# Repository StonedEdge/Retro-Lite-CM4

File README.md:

# Retro Lite CM4: Raspberry Pi Handheld

## Description
 
The Retro Lite CM4 is a joint project between Dmcke5 and StonedEdge. The console is powered by a 4000mAh Li-Po and is designed to run with various software images, including but not limited to RetroPie, Lakka or Batocera, directly from an SD card or via eMMC storage. The project housing was inspired by a Nintendo Switch Lite, but is not a 100% match to the original. The CM4 cannot currently emulate most 32/64-bit consoles released after the PSP or Dreamcast. This means GameCube, Wii and 3DS are currently unplayable until the Foundation releases a newer version of the Compute Module line. wiringPi is now a deprecated GPIO library however does work with arm64 and aarch64, so you can install 64-bit RetroPie if you'd like. 

## Features

- Machined aluminum 6061 housing (green/purple), custom machined and anodized by Dmcke5
- Raspberry Pi 4 SoC: Broadcom BCM2711 quad-core Cortex-A72 @ 1.5GHz (ARM CPU overclockable to 2.1GHz, GPU overclockable to 850MHz)
- 2GB of LPDDR4-3200 SDRAM
- 5.0GHz IEEE 802.11b/g/n/ac wireless, Bluetooth 5.0
- Custom AIO 4-layer PCB, with CM4 mezzanines, 5v boost rated at 2.1A continuous current, 3.3v buck, USB2422 hub, BQ24292i, MAX17055 fuel gauge, ATtiny84, WM8960 amp, TFP401 encoder, SD card slot, USB-C hardware and mini HDMI type A
- 2x controller PCBs with FFC cables
- 800 x 480 (5:3 aspect ratio) IPS display
- HDMI video output (HDMI0 - internal)
- 1080p 60fps HDMI video output (HDMI1 - external) via the mini HDMI port
- Tempered glass screen protector
- Fuel gauge for accurate battery SoC monitoring - MAX17055, custom battery indicator shown in steps of 10 icons, plus %SoC value, via dispmanx APIs on a TFT HDMI driven panel
- Charging indicator
- HDMI switching scripts, to shutdown and reboot to external HDMI with an overclock applied
- ATMEGA32u4 internal USB 2.0 HID controller
- Brightness and volume HUD adjustment, in steps of 10 icons. Brightness is adjusted by holding select + up/down on the DPAD
- Custom menu, activated by pushing select + R3. The menu consists of 4 sections (1. Battery Information, 2. Controller Calibration, 3. Onscreen Keyboard, 4. Settings Menu) -   courtesy of Dmcke5's hard work and ideas :D
- USB-C PD charging capabilities up to 15v (0.5C charge rate at 2A) with an original Nintendo Switch charger
- Stereo Audio Output via i2s WM8960 Wolfson audio amplifier
- Headphone jack, with automatic switching
- 4000mAh custom lipo design, providing 4 hours of gameplay
- Dual stacked shoulder buttons (L, R, LZ, RZ)
- 2x switch analog sticks, range programmable in software
- Resin casted ABXY, DPAD, start+select, shoulder buttons with acetal spring hinge + silicone membranes
- Safe software/hardware shutdown to prevent corruption to the SD card data (low voltage shutdown included)
- USB 2.0 2-port downstream hub
- External dock passthrough PCB with 4 port USB-hub - have now started uploading dock assets

Click the link below to view a more detailed buildlog of the Retro Lite CM4: 
https://bitbuilt.net/forums/index.php?threads/retro-lite-cm4-a-stonededge-and-dmcke5-collaboration.3934/

## Requirements to Build the Retro Lite CM4

### Code 

Code has now been split into various header files and the retrolite.c code has now been made easier to read and condensed for the end-user. Code required to complete the handheld includes an ATtiny84 monitor script, which can be flashed via the 1.27mm pitch 6 pin header on the main Retro Lite PCB with an Arduino or similar programmer. Code for the i2s audio amplifier, fuel gauge and OSD functionality can be compiled directly on the CM4 module from the command line. Current code is unfinished as of January 2022, however we are pushing bug fixes when we find them - expect a fully functioning RetroPie image to be shared in the future from this repository (actually, just found out this is not allowed due to the licensing of certain emulators, so will create install scripts at a later date). 

To flash the software to the Retro Lite CM4, you can either download the latest RetroPie Retro Lite custom image, or follow the below steps to get up and running. Plan is to eventually put this into a single script. I have not currently tested our firmware on images other than RetroPie, however I assume other images should also work fine. 

a) Download the latest version of RetroPie for the Raspberry Pi 4/400 here (also compatible with CM4): 
https://retropie.org.uk/download/ 

b) Run the WM8960 I2S audio amplifier script and install audio drivers:
https://github.com/StonedEdge/seeed-voicecard

c) Install the latest version of WiringPi, compatible with both 64/32-bit OS here: 
https://github.com/StonedEdge/WiringPi

d) Add config.txt to the /boot directory (overwrite)

e) cd /home/pi/RetroliteOSD sudo make - compile the Retro Lite CM4 C code and generate binary

f) Navigate to the /etc directory and add the below lines to the rc.local file, to allow the code to run every time at startup 

cd /home/pi/RetroliteOSD
sudo ./retrolite &
sudo ./hdmi_script.sh & 

g) sudo reboot - Reboot to enable all changes 

You should now have all the required software installed for the Retro Lite CM4 to display battery SoC, charging status, WiFi status, bluetooth status and more. The Retro Lite CM4 automatically safely shuts itself down when the voltage of the batteries depletes to 3.1V - adjustable directly from the settings calibration menu. The Retro Lite CM4 must reboot to output video to an external monitor via the mini HDMI type-A port, which is handled by the hdmi_switch.sh script. 

-------------------------------------------------------------------------------------------------------

### CAD
The CAD files for the Retro Lite CM4 are now available and open source! Please do give credit where due as a lot of work has gone into these designs.
You can check out my project partner's work here: https://github.com/dmcke5

-------------------------------------------------------------------------------------------------------

### PCB
The Retro Lite CM4 requires 4 custom designed PCBs to be installed, not including the CM4 carrier board. These include: 

a) Retro Lite CM4 AIO carrier board 

b) Retro Lite Controller PCB (Right)

c) Retro Lite Controller PCB (Left)

d) Retro Lite Button Daughterboard

Gerbers to be ordered from your board house of choice have now been uploaded! Recommended to use JLCPCB for fast turnaround using their 4-layer service.

-------------------------------------------------------------------------------------------------------

### BOM (Bill of Materials) 
Preliminary BOMs for all 4 PCBs have been added including cost. You will have to source your own parts however most can be found on Digikey/Mouser.

-------------------------------------------------------------------------------------------------------
### New Revision Features
Features that I would like to add to the handheld (welcome for others to assist) include the following:

a) HDMI over USB-C, using the TPS65987D and the TUSB546A-DCI high speed mux. 

b) OTG integration (power perihperals through the onboard USB-C port). 

c) DSI 5.5" display (struggle to know of a way to get this working currently on the Pi). 

Feel free to make a pull request with any changes you would like seen to the handheld. 

-------------------------------------------------------------------------------------------------------

### FAQs
Q: How can I get my hands one of these handhelds? Do you sell them? 

A: I am not currently selling kits on this handheld (nor do I plan to for the forseeable future), but I do offer commissions on occassion via my social media. DM me for details. 

Q: Why dont you use a 5.5" display from a Switch Lite? 

A: MIPI reverse engineering is not simple not trivial to a hobbyist like myself. 

Q: Why are your commissions ludicrously priced?

A: Building one off handhelds for people is expensive. Labor & parts dont come cheap either. I'd recommend you build one yourself using the assets from this GitHub or just buy a mass produced emulation handheld from Aliexpress. 

### Optional Docking Station 

Source code available here:
https://github.com/StonedEdge/Retro-Lite-CM4-Dock

The docking station is now completed! It's designed to work with RetroPie and use a RP2040 microcontroller, written in C (Pico) and Python (CM4). Feel free to build one if you'd like! 

-------------------------------------------------------------------------------------------------------
### Contributors 
I'd like to thank these people in no particular order for the awesome work you have done to help me complete this project. 

* Dmcke5 for designing the case assets, including machining/anodizing the prototypes, doing most of the code and much more. Wouldn't have been possible to complete this without you - a team effort
* YveltalGriffin/Mackie-Kannard Smith, for suggesting various hardware changes and reviews to PCB/schematics + GitHub bugs. His help was invaluable in learning new things about PCB design 
* Juckett D, for creating the Aegis CM4 and offering tips and tricks along the way. Check out his work here and awesome CM4 handheld(s): https://github.com/juckettd
* Aurelio Manarra, for always helping me out with my non EE questions and various other things ᕕ( ᐛ )ᕗ
* Bill, for helping me with the docking station code & bug fixes

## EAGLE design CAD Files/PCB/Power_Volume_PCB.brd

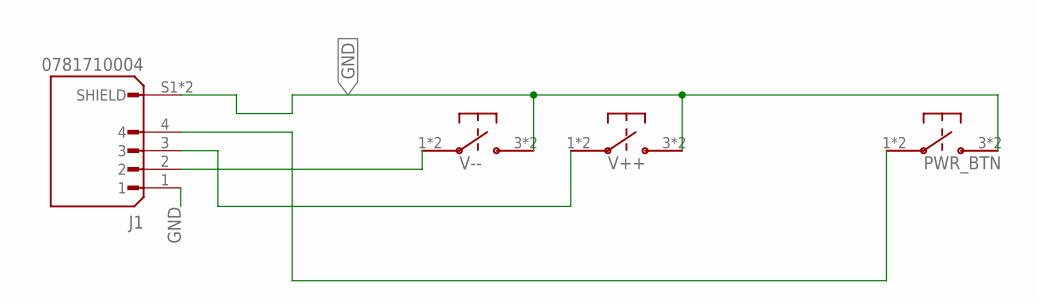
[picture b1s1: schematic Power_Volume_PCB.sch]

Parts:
J1: 0781710004; MOLEX_0781710004
PWR_BTN: TL3315NF100Q
V++: TL3315NF100Q
V--: TL3315NF100Q

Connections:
GND: J1.1, J1.S1 (SHIELD), J1.S2 (SHIELD), PWR_BTN.3, PWR_BTN.4, V++.3, V++.4, V--.3, V--.4
unnamed: J1.4, PWR_BTN.1, PWR_BTN.2
unnamed: J1.3, V++.1, V++.2
unnamed: J1.2, V--.1, V--.2

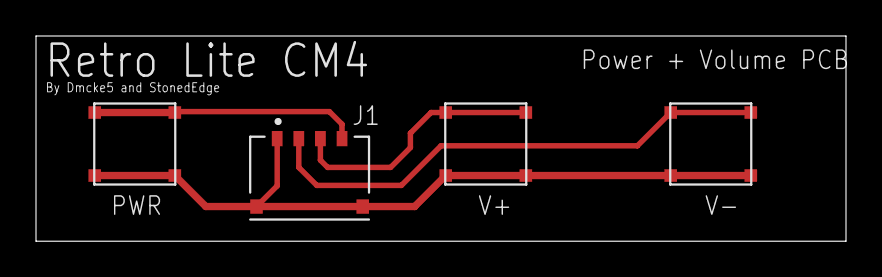
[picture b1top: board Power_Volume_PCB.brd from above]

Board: 2 copper layers, 45.0 x 11.4 mm, 4 parts (0 on the bottom side), 4 nets.

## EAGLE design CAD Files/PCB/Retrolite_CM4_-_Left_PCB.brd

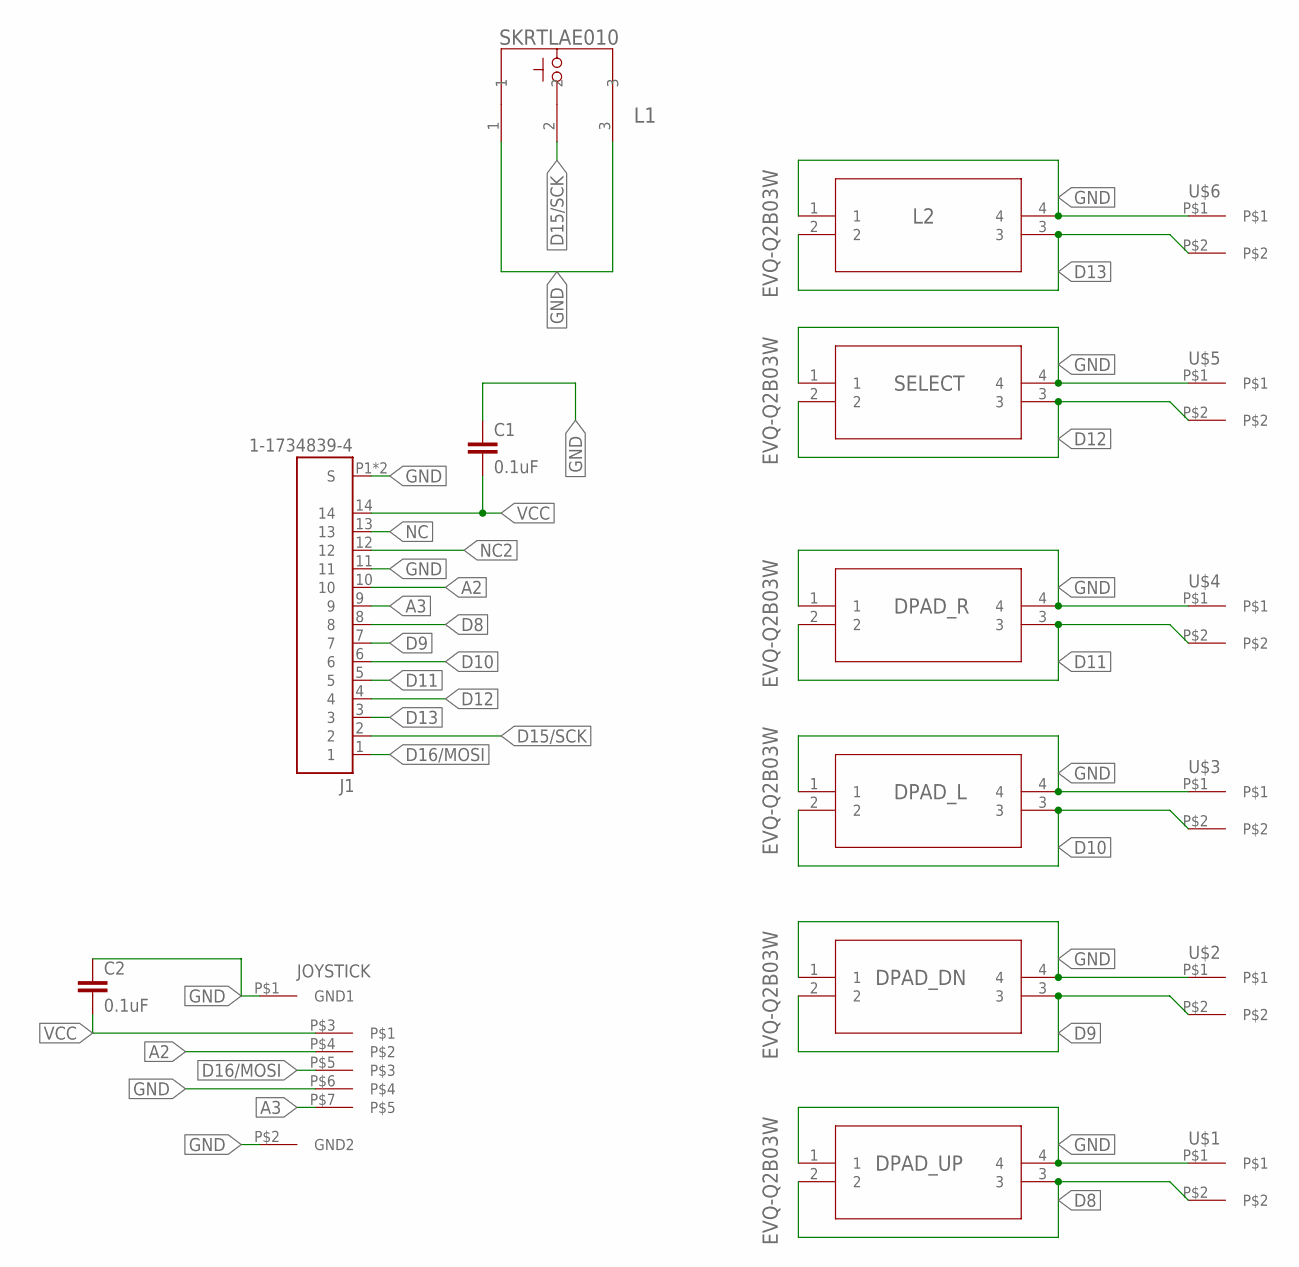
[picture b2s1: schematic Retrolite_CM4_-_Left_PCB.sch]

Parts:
C1, C2: 0.1uF; 0603
DPAD_DN: EVQ-Q2B03W; EVQQ2_3
DPAD_L: EVQ-Q2B03W; EVQQ2_3
DPAD_R: EVQ-Q2B03W; EVQQ2_3
DPAD_UP: EVQ-Q2B03W; EVQQ2_3
J1: 1-1734839-4; TE_1-1734839-4
JOYSTICK: 0545500571
L1: SKRTLAE010; SW3_SKRTLAE010_ALPS
L2: EVQ-Q2B03W; EVQQ2_3
SELECT: EVQ-Q2B03W; EVQQ2_3
U$1, U$2, U$3, U$4, U$5, U$6: MEMBRANEBUTTON

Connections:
A2: J1.10, JOYSTICK.P$4
A3: J1.9, JOYSTICK.P$7
D8: DPAD_UP.2, DPAD_UP.3, J1.8, U$1.P$2
D9: DPAD_DN.2, DPAD_DN.3, J1.7, U$2.P$2
D10: DPAD_L.2, DPAD_L.3, J1.6, U$3.P$2
D11: DPAD_R.2, DPAD_R.3, J1.5, U$4.P$2
D12: J1.4, SELECT.2, SELECT.3, U$5.P$2
D13: J1.3, L2.2, L2.3, U$6.P$2
D15/SCK: J1.2, L1.2
D16/MOSI: J1.1, JOYSTICK.P$5
GND: C1.1, C2.1, DPAD_DN.1, DPAD_DN.4, DPAD_L.1, DPAD_L.4, DPAD_R.1, DPAD_R.4, DPAD_UP.1, DPAD_UP.4, J1.11, J1.P1 (S), J1.P2 (S), JOYSTICK.P$1 (GND1), JOYSTICK.P$2 (GND2), JOYSTICK.P$6, L1.1, L1.3, L2.1, L2.4, SELECT.1, SELECT.4, U$1.P$1, U$2.P$1, U$3.P$1, U$4.P$1, U$5.P$1, U$6.P$1
NC: J1.13
NC2: J1.12
VCC: C1.2, C2.2, J1.14, JOYSTICK.P$3

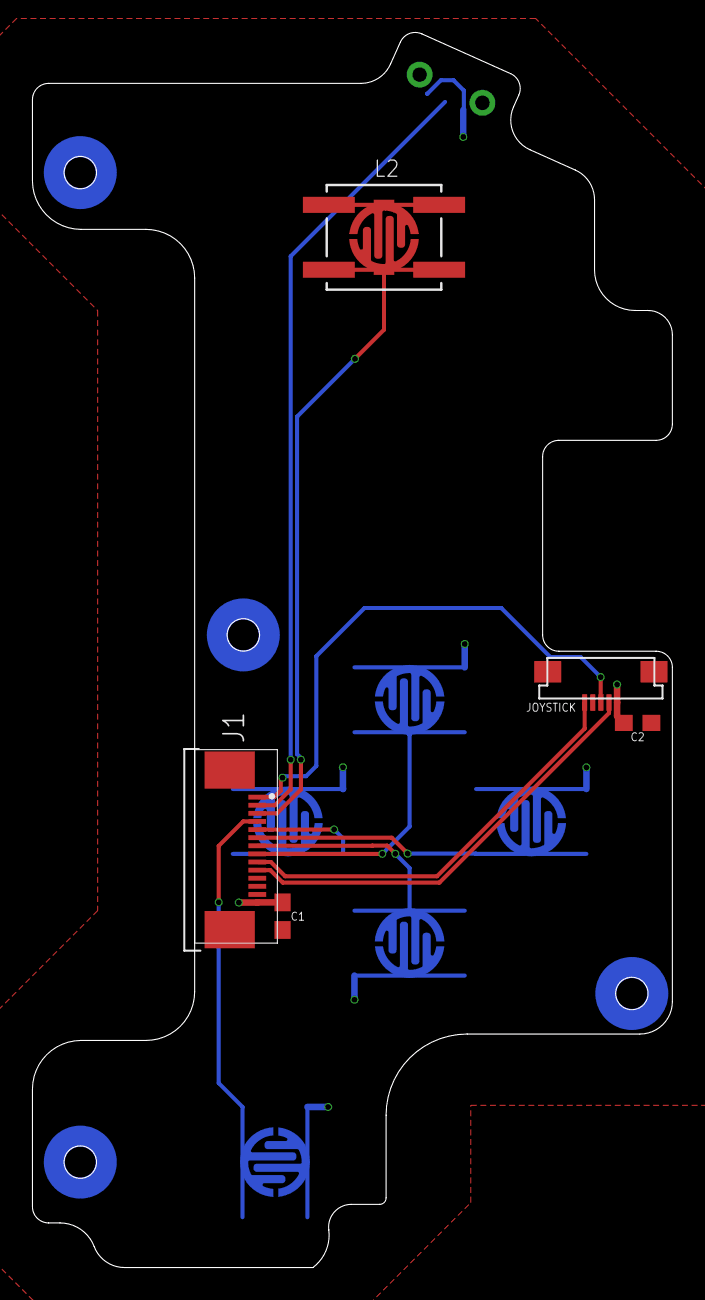
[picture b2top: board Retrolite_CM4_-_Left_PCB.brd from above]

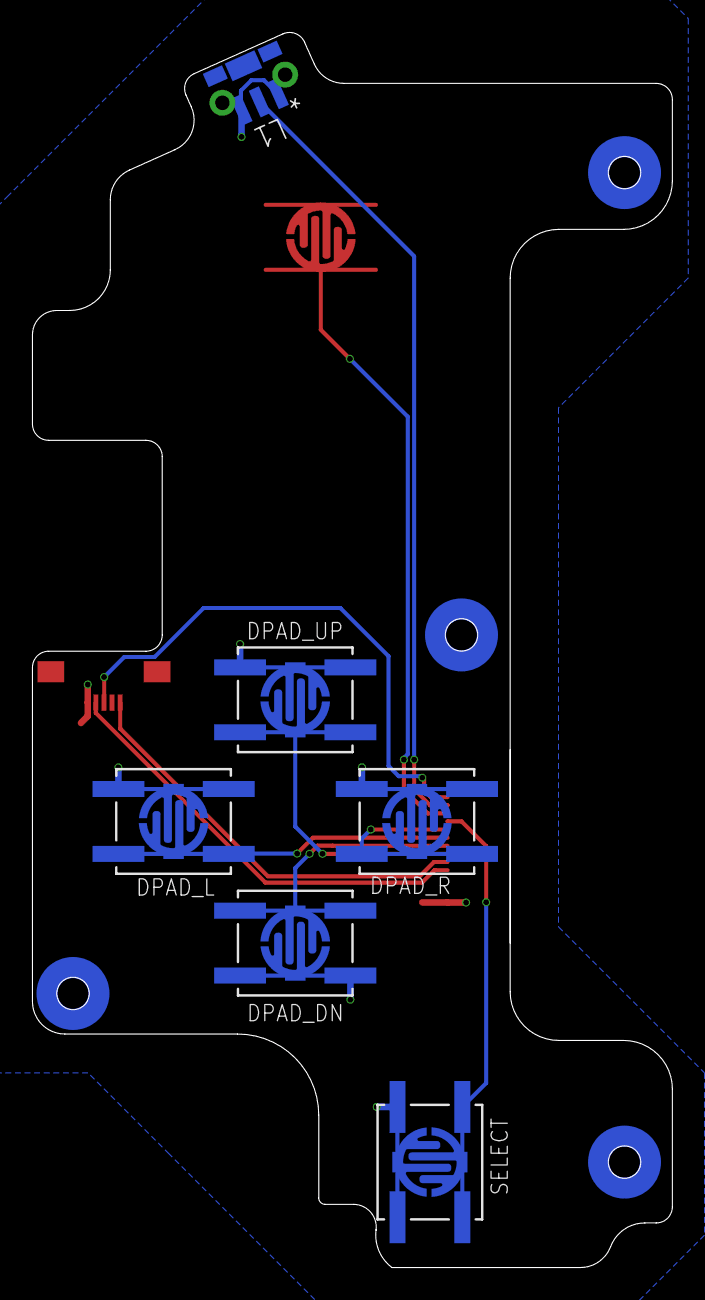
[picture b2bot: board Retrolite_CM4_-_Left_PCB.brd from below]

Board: 2 copper layers, 39.5 x 76.1 mm, 17 parts (11 on the bottom side), 12 nets.

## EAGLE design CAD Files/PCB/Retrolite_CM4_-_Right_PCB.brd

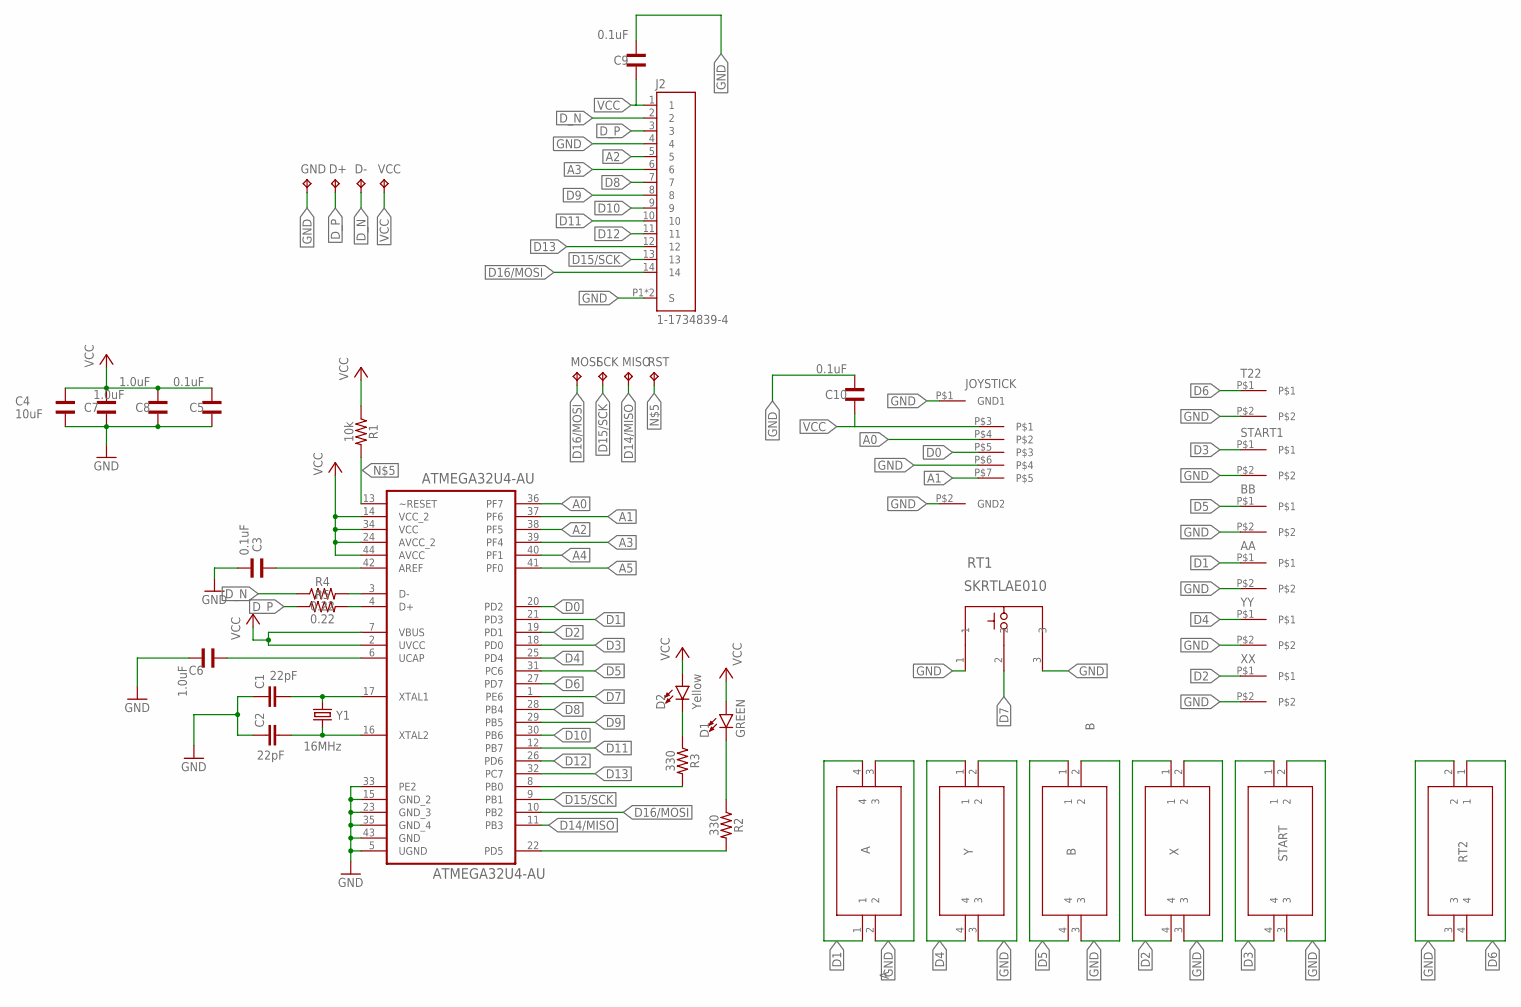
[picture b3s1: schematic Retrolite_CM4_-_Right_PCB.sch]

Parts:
A: A; EVQQ2_3
AA: MEMBRANEBUTTON
ATMEGA32U4-AU: ATMEGA32U4-AU; QFP80P1200X1200X120-44N
B: B; EVQQ2_3
BB: MEMBRANEBUTTON
C1, C2: 22pF; 0603
C3, C5, C9, C10: 0.1uF; WCAP-CSGP_0805_WAVE
C4: 10uF; WCAP-CSGP_0805_WAVE
C6, C7, C8: 1.0uF; WCAP-CSGP_0805_WAVE
D1: GREEN; LED-0603
D2: Yellow; LED-0603
D+: TPB1,27; B1,27
D-: TPB1,27; B1,27
GND: TPB1,27; B1,27
J2: 1-1734839-4; TE_1-1734839-4
JOYSTICK: 0545500571
MISO: TPB1,27; B1,27
MOSI: TPB1,27; B1,27
R1: 10k; 0603
R2, R3: 330; 0603
R4, R5: 0.22; 0805
RST: TPB1,27; B1,27
RT1: SKRTLAE010; SW3_SKRTLAE010_ALPS
RT2: T2; EVQQ2_3
SCK: TPB1,27; B1,27
START: START; EVQQ2_3
START1: MEMBRANEBUTTON
T22: MEMBRANEBUTTON
VCC: TPB1,27; B1,27
X: X; EVQQ2_3
XX: MEMBRANEBUTTON
Y: Y; EVQQ2_3
Y1: 16MHz; CRYSTAL-SMD-5X3.2-4PAD
YY: MEMBRANEBUTTON

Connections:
A0: ATMEGA32U4-AU.36 (PF7), JOYSTICK.P$4
A1: ATMEGA32U4-AU.37 (PF6), JOYSTICK.P$7
A2: ATMEGA32U4-AU.38 (PF5), J2.5
A3: ATMEGA32U4-AU.39 (PF4), J2.6
A4: ATMEGA32U4-AU.40 (PF1)
A5: ATMEGA32U4-AU.41 (PF0)
D0: ATMEGA32U4-AU.20 (PD2), JOYSTICK.P$5
D1: A.1, A.4, AA.P$1, ATMEGA32U4-AU.21 (PD3)
D2: ATMEGA32U4-AU.19 (PD1), X.1, X.4, XX.P$1
D3: ATMEGA32U4-AU.18 (PD0), START.1, START.4, START1.P$1
D4: ATMEGA32U4-AU.25 (PD4), Y.1, Y.4, YY.P$1
D5: ATMEGA32U4-AU.31 (PC6), B.1, B.4, BB.P$1
D6: ATMEGA32U4-AU.27 (PD7), RT2.1, RT2.4, T22.P$1
D7: ATMEGA32U4-AU.1 (PE6), RT1.2
D8: ATMEGA32U4-AU.28 (PB4), J2.7
D9: ATMEGA32U4-AU.29 (PB5), J2.8
D10: ATMEGA32U4-AU.30 (PB6), J2.9
D11: ATMEGA32U4-AU.12 (PB7), J2.10
D12: ATMEGA32U4-AU.26 (PD6), J2.11
D13: ATMEGA32U4-AU.32 (PC7), J2.12
D14/MISO: ATMEGA32U4-AU.11 (PB3), MISO.TP
D15/SCK: ATMEGA32U4-AU.9 (PB1), J2.13, SCK.TP
D16/MOSI: ATMEGA32U4-AU.10 (PB2), J2.14, MOSI.TP
D_N: D-.TP, J2.2, R4.1
D_P: D+.TP, J2.3, R5.1
GND: A.2, A.3, AA.P$2, ATMEGA32U4-AU.5 (UGND), ATMEGA32U4-AU.15 (GND_2), ATMEGA32U4-AU.23 (GND_3), ATMEGA32U4-AU.33 (PE2), ATMEGA32U4-AU.35 (GND_4), ATMEGA32U4-AU.43 (GND), B.2, B.3, BB.P$2, C1.1, C2.1, C3.1, C4.1, C5.2, C6.1, C7.2, C8.2, C9.1, C10.1, GND.TP, J2.4, J2.P1 (S), J2.P2 (S), JOYSTICK.P$1 (GND1), JOYSTICK.P$2 (GND2), JOYSTICK.P$6, RT1.1, RT1.3, RT2.2, RT2.3, START.2, START.3, START1.P$2, T22.P$2, X.2, X.3, XX.P$2, Y.2, Y.3, YY.P$2
unnamed: ATMEGA32U4-AU.17 (XTAL1), C1.2, Y1.1
unnamed: ATMEGA32U4-AU.42 (AREF), C3.2
unnamed: ATMEGA32U4-AU.6 (UCAP), C6.2
unnamed: ATMEGA32U4-AU.16 (XTAL2), C2.2, Y1.3 (2)
unnamed: ATMEGA32U4-AU.13 (~RESET), R1.2, RST.TP
unnamed: ATMEGA32U4-AU.22 (PD5), R2.2
unnamed: ATMEGA32U4-AU.8 (PB0), R3.2
unnamed: D1.C, R2.1
unnamed: D2.C, R3.1
USB_N: ATMEGA32U4-AU.3 (D-), R4.2
USB_P: ATMEGA32U4-AU.4 (D+), R5.2
VCC: ATMEGA32U4-AU.2 (UVCC), ATMEGA32U4-AU.7 (VBUS), ATMEGA32U4-AU.14 (VCC_2), ATMEGA32U4-AU.24 (AVCC_2), ATMEGA32U4-AU.34 (VCC), ATMEGA32U4-AU.44 (AVCC), C4.2, C5.1, C7.1, C8.1, C9.2, C10.2, D1.A, D2.A, J2.1, JOYSTICK.P$3, R1.1, VCC.TP

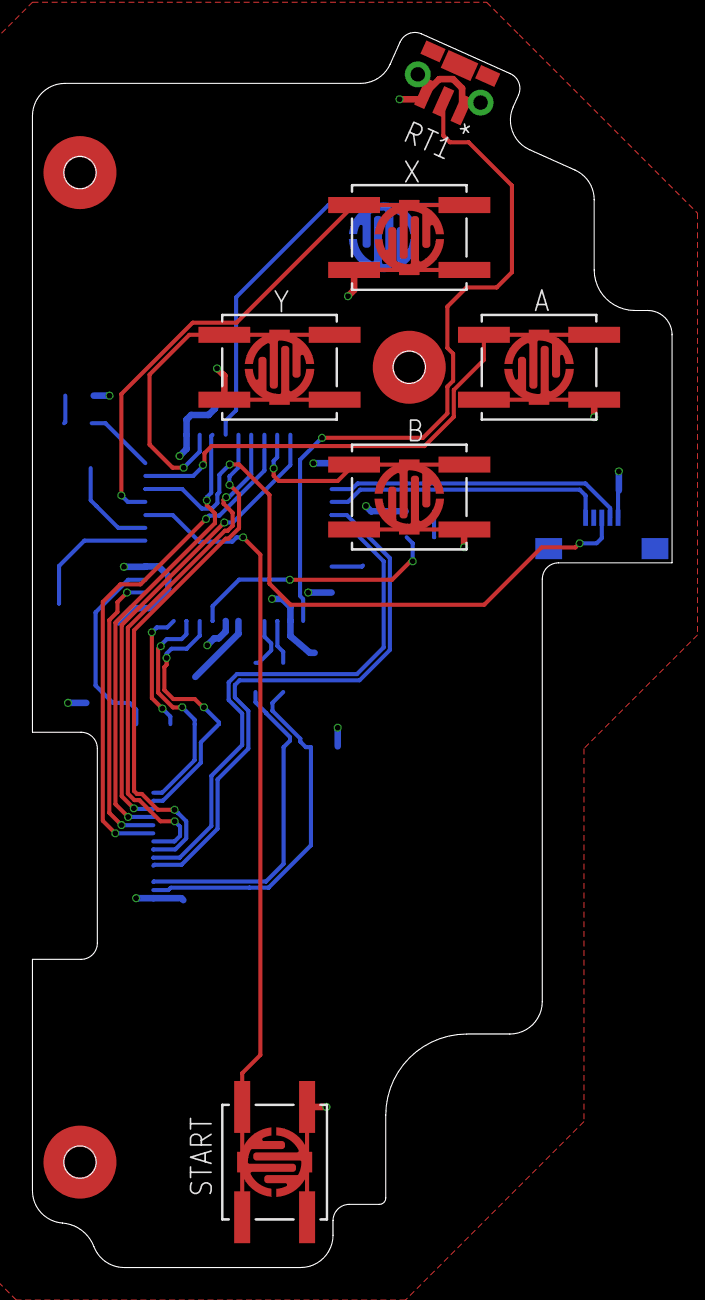
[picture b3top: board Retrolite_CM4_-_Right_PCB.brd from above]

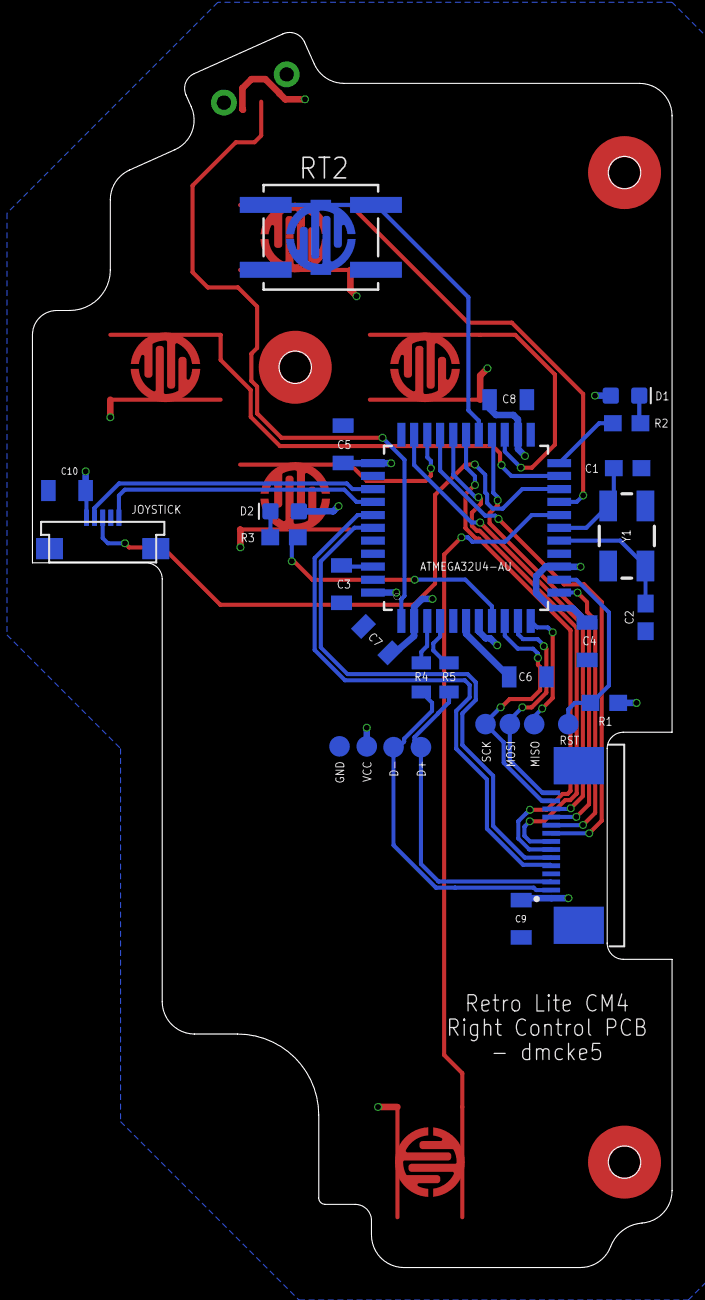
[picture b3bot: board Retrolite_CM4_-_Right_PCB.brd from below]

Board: 2 copper layers, 39.4 x 76.1 mm, 42 parts (31 on the bottom side), 36 nets.

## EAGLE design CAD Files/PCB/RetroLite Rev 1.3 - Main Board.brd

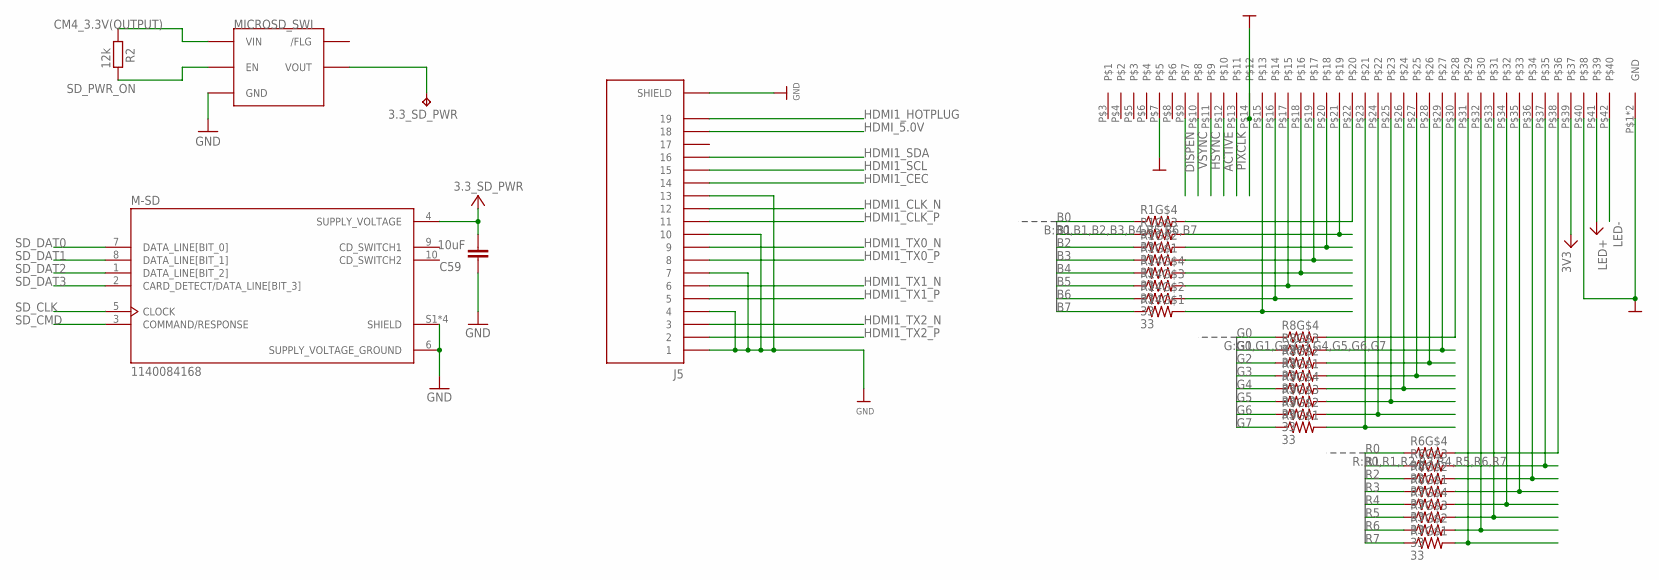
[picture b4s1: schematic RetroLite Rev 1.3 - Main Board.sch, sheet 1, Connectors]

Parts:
3.3_SD_PWR: TPTP07R; TP07R
C59: 10uF; 0805
J5: 685119136923; WURTH_685119136923
M-SD: 1140084168; AMPHENOL_1140084168
MICROSD_SWI: IC-RT9742
R1, R6, R7, R8, R9, R14: 33; RESPACK_4X0603
R2: 12k; R0603
U3: S62684-402100ALF

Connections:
3.3_SD_PWR: 3.3_SD_PWR.TP, C59.2, M-SD.4 (SUPPLY_VOLTAGE), MICROSD_SWI.VOUT
3V3: U3.P$39; also elsewhere on the board
ACTIVE: U3.P$12; also elsewhere on the board
B0: R1.4 (1); also elsewhere on the board
B1: R1.3 (1); also elsewhere on the board
B2: R1.2 (1); also elsewhere on the board
B3: R1.1; also elsewhere on the board
B4: R14.4 (1); also elsewhere on the board
B5: R14.3 (1); also elsewhere on the board
B6: R14.2 (1); also elsewhere on the board
B7: R14.1; also elsewhere on the board
CM4_3.3V(OUTPUT): MICROSD_SWI.VIN, R2.1; also elsewhere on the board
DISPEN: U3.P$9; also elsewhere on the board
G0: R8.4 (1); also elsewhere on the board
G1: R8.3 (1); also elsewhere on the board
G2: R8.2 (1); also elsewhere on the board
G3: R8.1; also elsewhere on the board
G4: R9.4 (1); also elsewhere on the board
G5: R9.3 (1); also elsewhere on the board
G6: R9.2 (1); also elsewhere on the board
G7: R9.1; also elsewhere on the board
GND: C59.1, J5.1, J5.4, J5.7, J5.10, J5.13, J5.S1 (SHIELD), J5.S2 (SHIELD), J5.S3 (SHIELD), J5.S4 (SHIELD), M-SD.6 (SUPPLY_VOLTAGE_GROUND), M-SD.S1 (SHIELD), M-SD.S2 (SHIELD), M-SD.S3 (SHIELD), M-SD.S4 (SHIELD), MICROSD_SWI.GND, U3.P$1 (GND), U3.P$2 (GND), U3.P$7, U3.P$14, U3.P$40; also elsewhere on the board
HDMI1_CEC: J5.14; also elsewhere on the board
HDMI1_CLK_N: J5.12; also elsewhere on the board
HDMI1_CLK_P: J5.11; also elsewhere on the board
HDMI1_HOTPLUG: J5.19; also elsewhere on the board
HDMI1_SCL: J5.15; also elsewhere on the board
HDMI1_SDA: J5.16; also elsewhere on the board
HDMI1_TX0_N: J5.9; also elsewhere on the board
HDMI1_TX0_P: J5.8; also elsewhere on the board
HDMI1_TX1_N: J5.6; also elsewhere on the board
HDMI1_TX1_P: J5.5; also elsewhere on the board
HDMI1_TX2_N: J5.3; also elsewhere on the board
HDMI1_TX2_P: J5.2; also elsewhere on the board
HDMI_5.0V: J5.18; also elsewhere on the board
HSYNC: U3.P$11; also elsewhere on the board
LED+: U3.P$41; also elsewhere on the board
LED-: U3.P$42; also elsewhere on the board
unnamed: R8.5 (2), U3.P$30
unnamed: R8.6 (2), U3.P$29
unnamed: R8.7 (2), U3.P$28
unnamed: R8.8 (2), U3.P$27
unnamed: R9.5 (2), U3.P$26
unnamed: R9.6 (2), U3.P$25
unnamed: R6.5 (2), U3.P$38
unnamed: R6.6 (2), U3.P$37
unnamed: R6.7 (2), U3.P$36
unnamed: R6.8 (2), U3.P$35
unnamed: R7.5 (2), U3.P$34
unnamed: R7.6 (2), U3.P$33
unnamed: R7.7 (2), U3.P$32
unnamed: R7.8 (2), U3.P$31
unnamed: R9.7 (2), U3.P$24
unnamed: R9.8 (2), U3.P$23
unnamed: R1.5 (2), U3.P$22
unnamed: R1.6 (2), U3.P$21
unnamed: R1.7 (2), U3.P$20
unnamed: R1.8 (2), U3.P$19
unnamed: R14.8 (2), U3.P$15
unnamed: R14.7 (2), U3.P$16
unnamed: R14.6 (2), U3.P$17
unnamed: R14.5 (2), U3.P$18
PIXCLK: U3.P$13; also elsewhere on the board
R0: R6.4 (1); also elsewhere on the board
R1: R6.3 (1); also elsewhere on the board
R2: R6.2 (1); also elsewhere on the board
R3: R6.1; also elsewhere on the board
R4: R7.4 (1); also elsewhere on the board
R5: R7.3 (1); also elsewhere on the board
R6: R7.2 (1); also elsewhere on the board
R7: R7.1; also elsewhere on the board
SD_CLK: M-SD.5 (CLOCK); also elsewhere on the board
SD_CMD: M-SD.3 (COMMAND/RESPONSE); also elsewhere on the board
SD_DAT0: M-SD.7 (DATA_LINE[BIT_0]); also elsewhere on the board
SD_DAT1: M-SD.8 (DATA_LINE[BIT_1]); also elsewhere on the board
SD_DAT2: M-SD.1 (DATA_LINE[BIT_2]); also elsewhere on the board
SD_DAT3: M-SD.2 (CARD_DETECT/DATA_LINE[BIT_3]); also elsewhere on the board
SD_PWR_ON: MICROSD_SWI.EN, R2.2; also elsewhere on the board
VSYNC: U3.P$10; also elsewhere on the board

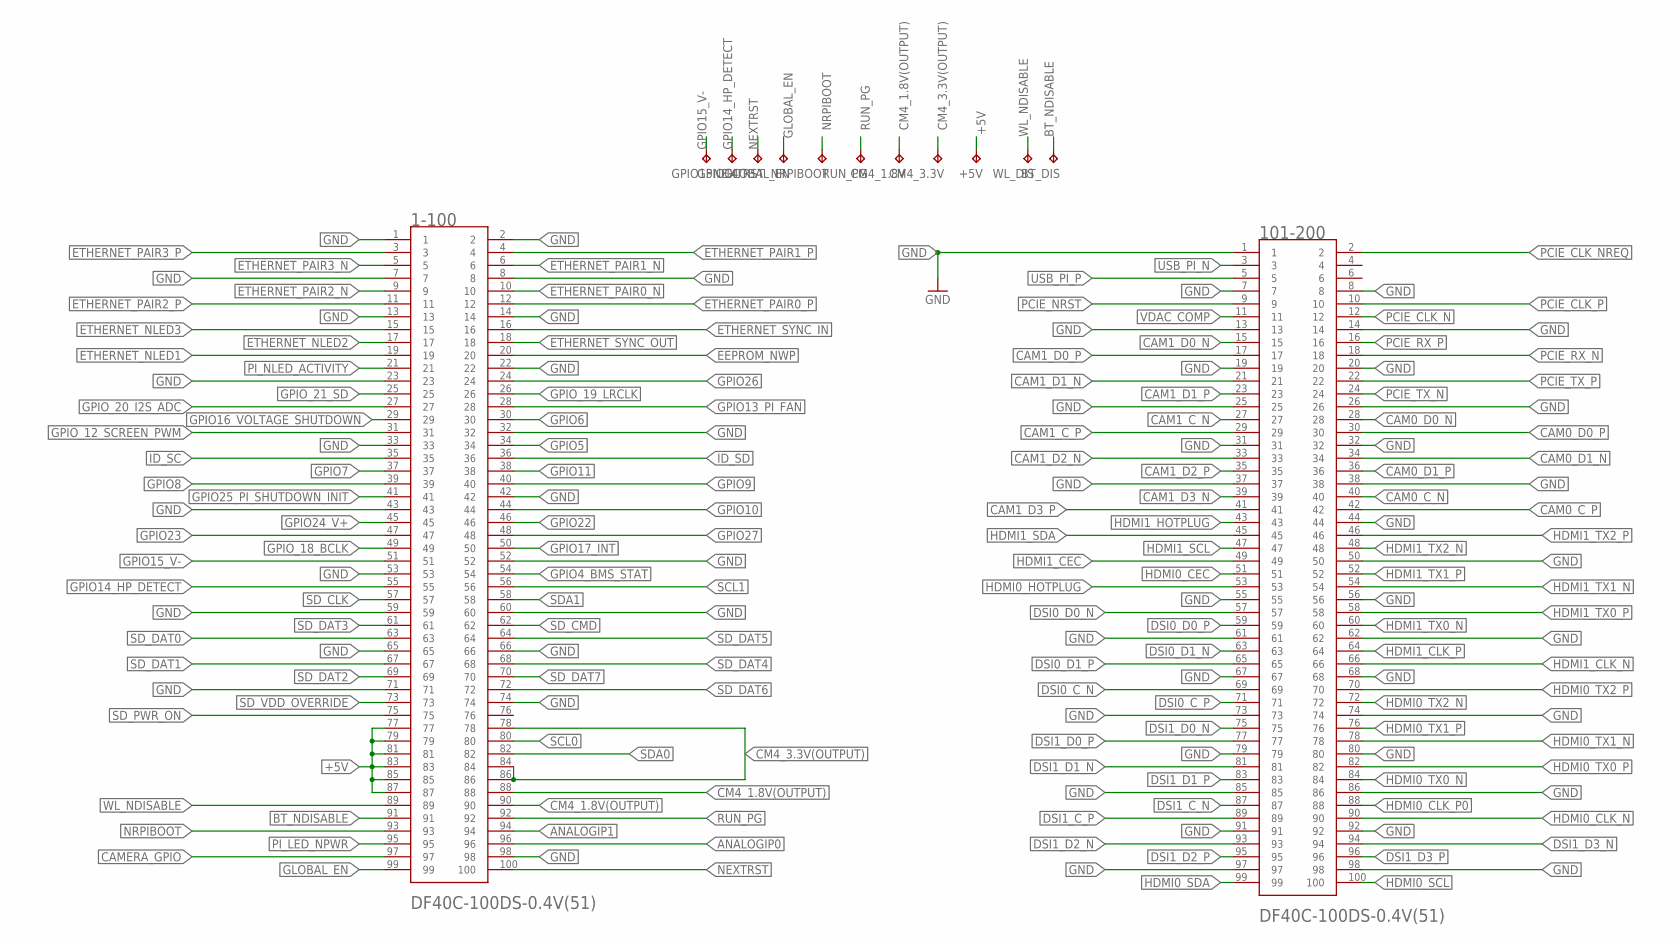
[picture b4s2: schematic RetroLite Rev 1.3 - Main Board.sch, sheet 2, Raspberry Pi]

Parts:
1-100, 101-200: DF40C-100DS-0.4V(51); HRS_DF40C-100DS-0.4V(51)
+5V: TPTP07R; TP07R
BT_DIS: TPTP07R; TP07R
CM4_1.8V, CM4_3.3V: TPTP07R; TP07R
GLOBAL_EN: TPTP07R; TP07R
GPIO14, GPIO15: TPTP07R; TP07R
NEXTRST: TPTP07R; TP07R
NRPIBOOT: TPTP07R; TP07R
RUN_PG: TPTP07R; TP07R
WL_DIS: TPTP07R; TP07R

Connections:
+5V: 1-100.77, 1-100.79, 1-100.81, 1-100.83, 1-100.85, 1-100.87, +5V.TP; also elsewhere on the board
ANALOGIP0: 1-100.96
ANALOGIP1: 1-100.94
BT_NDISABLE: 1-100.91, BT_DIS.TP
CAM0_C_N: 101-200.40
CAM0_C_P: 101-200.42
CAM0_D0_N: 101-200.28
CAM0_D0_P: 101-200.30
CAM0_D1_N: 101-200.34
CAM0_D1_P: 101-200.36
CAM1_C_N: 101-200.27
CAM1_C_P: 101-200.29
CAM1_D0_N: 101-200.15
CAM1_D0_P: 101-200.17
CAM1_D1_N: 101-200.21
CAM1_D1_P: 101-200.23
CAM1_D2_N: 101-200.33
CAM1_D2_P: 101-200.35
CAM1_D3_N: 101-200.39
CAM1_D3_P: 101-200.41
CAMERA_GPIO: 1-100.97
CM4_1.8V(OUTPUT): 1-100.88, 1-100.90, CM4_1.8V.TP
CM4_3.3V(OUTPUT): 1-100.78, 1-100.84, 1-100.86, CM4_3.3V.TP; also elsewhere on the board
DSI0_C_N: 101-200.69
DSI0_C_P: 101-200.71
DSI0_D0_N: 101-200.57
DSI0_D0_P: 101-200.59
DSI0_D1_N: 101-200.63
DSI0_D1_P: 101-200.65
DSI1_C_N: 101-200.87
DSI1_C_P: 101-200.89
DSI1_D0_N: 101-200.75
DSI1_D0_P: 101-200.77
DSI1_D1_N: 101-200.81
DSI1_D1_P: 101-200.83
DSI1_D2_N: 101-200.93
DSI1_D2_P: 101-200.95
DSI1_D3_N: 101-200.94
DSI1_D3_P: 101-200.96
EEPROM_NWP: 1-100.20
ETHERNET_NLED1: 1-100.19
ETHERNET_NLED2: 1-100.17
ETHERNET_NLED3: 1-100.15
ETHERNET_PAIR0_N: 1-100.10
ETHERNET_PAIR0_P: 1-100.12
ETHERNET_PAIR1_N: 1-100.6
ETHERNET_PAIR1_P: 1-100.4
ETHERNET_PAIR2_N: 1-100.9
ETHERNET_PAIR2_P: 1-100.11
ETHERNET_PAIR3_N: 1-100.5
ETHERNET_PAIR3_P: 1-100.3
ETHERNET_SYNC_IN: 1-100.16
ETHERNET_SYNC_OUT: 1-100.18
GLOBAL_EN: 1-100.99, GLOBAL_EN.TP; also elsewhere on the board
GND: 1-100.1, 1-100.2, 1-100.7, 1-100.8, 1-100.13, 1-100.14, 1-100.22, 1-100.23, 1-100.32, 1-100.33, 1-100.42, 1-100.43, 1-100.52, 1-100.53, 1-100.59, 1-100.60, 1-100.65, 1-100.66, 1-100.71, 1-100.74, 1-100.98, 101-200.1, 101-200.7, 101-200.8, 101-200.13, 101-200.14, 101-200.19, 101-200.20, 101-200.25, 101-200.26, 101-200.31, 101-200.32, 101-200.37, 101-200.38, 101-200.44, 101-200.50, 101-200.55, 101-200.56, 101-200.61, 101-200.62, 101-200.67, 101-200.68, 101-200.73, 101-200.74, 101-200.79, 101-200.80, 101-200.85, 101-200.86, 101-200.91, 101-200.92, 101-200.97, 101-200.98; also elsewhere on the board
GPIO4_BMS_STAT: 1-100.54; also elsewhere on the board
GPIO5: 1-100.34
GPIO6: 1-100.30
GPIO7: 1-100.37
GPIO8: 1-100.39
GPIO9: 1-100.40
GPIO10: 1-100.44
GPIO11: 1-100.38
GPIO13_PI_FAN: 1-100.28; also elsewhere on the board
GPIO14_HP_DETECT: 1-100.55, GPIO14.TP; also elsewhere on the board
GPIO15_V-: 1-100.51, GPIO15.TP; also elsewhere on the board
GPIO16_VOLTAGE_SHUTDOWN: 1-100.29; also elsewhere on the board
GPIO17_INT: 1-100.50; also elsewhere on the board
GPIO22: 1-100.46
GPIO23: 1-100.47
GPIO24_V+: 1-100.45; also elsewhere on the board
GPIO25_PI_SHUTDOWN_INIT: 1-100.41; also elsewhere on the board
GPIO26: 1-100.24
GPIO27: 1-100.48
GPIO_12_SCREEN_PWM: 1-100.31; also elsewhere on the board
GPIO_18_BCLK: 1-100.49; also elsewhere on the board
GPIO_19_LRCLK: 1-100.26; also elsewhere on the board
GPIO_20_I2S_ADC: 1-100.27; also elsewhere on the board
GPIO_21_SD: 1-100.25; also elsewhere on the board
HDMI0_CEC: 101-200.51
HDMI0_CLK_N: 101-200.90; also elsewhere on the board
HDMI0_CLK_P0: 101-200.88; also elsewhere on the board
HDMI0_HOTPLUG: 101-200.53
HDMI0_SCL: 101-200.100; also elsewhere on the board
HDMI0_SDA: 101-200.99; also elsewhere on the board
HDMI0_TX0_N: 101-200.84; also elsewhere on the board
HDMI0_TX0_P: 101-200.82; also elsewhere on the board
HDMI0_TX1_N: 101-200.78; also elsewhere on the board
HDMI0_TX1_P: 101-200.76; also elsewhere on the board
HDMI0_TX2_N: 101-200.72; also elsewhere on the board
HDMI0_TX2_P: 101-200.70; also elsewhere on the board
HDMI1_CEC: 101-200.49; also elsewhere on the board
HDMI1_CLK_N: 101-200.66; also elsewhere on the board
HDMI1_CLK_P: 101-200.64; also elsewhere on the board
HDMI1_HOTPLUG: 101-200.43; also elsewhere on the board
HDMI1_SCL: 101-200.47; also elsewhere on the board
HDMI1_SDA: 101-200.45; also elsewhere on the board
HDMI1_TX0_N: 101-200.60; also elsewhere on the board
HDMI1_TX0_P: 101-200.58; also elsewhere on the board
HDMI1_TX1_N: 101-200.54; also elsewhere on the board
HDMI1_TX1_P: 101-200.52; also elsewhere on the board
HDMI1_TX2_N: 101-200.48; also elsewhere on the board
HDMI1_TX2_P: 101-200.46; also elsewhere on the board
ID_SC: 1-100.35
ID_SD: 1-100.36
NEXTRST: 1-100.100, NEXTRST.TP
NRPIBOOT: 1-100.93, NRPIBOOT.TP
PCIE_CLK_N: 101-200.12
PCIE_CLK_NREQ: 101-200.2
PCIE_CLK_P: 101-200.10
PCIE_NRST: 101-200.9
PCIE_RX_N: 101-200.18
PCIE_RX_P: 101-200.16
PCIE_TX_N: 101-200.24
PCIE_TX_P: 101-200.22
PI_LED_NPWR: 1-100.95; also elsewhere on the board
PI_NLED_ACTIVITY: 1-100.21; also elsewhere on the board
RUN_PG: 1-100.92, RUN_PG.TP; also elsewhere on the board
SCL0: 1-100.80
SCL1: 1-100.56; also elsewhere on the board
SDA0: 1-100.82
SDA1: 1-100.58; also elsewhere on the board
SD_CLK: 1-100.57; also elsewhere on the board
SD_CMD: 1-100.62; also elsewhere on the board
SD_DAT0: 1-100.63; also elsewhere on the board
SD_DAT1: 1-100.67; also elsewhere on the board
SD_DAT2: 1-100.69; also elsewhere on the board
SD_DAT3: 1-100.61; also elsewhere on the board
SD_DAT4: 1-100.68
SD_DAT5: 1-100.64
SD_DAT6: 1-100.72
SD_DAT7: 1-100.70
SD_PWR_ON: 1-100.75; also elsewhere on the board
SD_VDD_OVERRIDE: 1-100.73
USB_PI_N: 101-200.3; also elsewhere on the board
USB_PI_P: 101-200.5; also elsewhere on the board
VDAC_COMP: 101-200.11
WL_NDISABLE: 1-100.89, WL_DIS.TP

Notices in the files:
parts and their libraries:
microbuilder: This work is placed in the public domain, and may be freely used for commercial and non-commercial work with the following conditions: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
SparkFun-Capacitors: Licensing: Creative Commons ShareAlike 4.0 International - https://creativecommons.org/licenses/by-sa/4.0
